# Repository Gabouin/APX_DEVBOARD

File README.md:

<h1 align="center">
  <br>
  
  <br>
  APX DEVBOARD
  <br>
</h1>

<h4 align="center">
A STM32 based devboard with Buttons, a LED and 8 GPIO pins.
</h4>

<div align="center">

</div>

<p align="center">
  <a href="#about-the-project">About</a> •
  <a href="#repository-structure">Structure</a> •
  <a href="#schematic-on-kicad">Schematic</a> •
  <a href="#pcb-on-kicad">PCB</a> •
  <a href="#CAD">CAD</a> •
  <a href="#bill-of-materials">BOM</a> •
  <a href="#license">License</a> •
  <a href="#credits">Credits</a>
</p>

<br>
<br>

## About the Project

**APX DEVBOARD** is a STM32 based devboard designed with GPIO pins, buttons and an LED

### Features

- **STM32G431CBT6** MCU 32-Bit 170MHz 128KB (128K x 8) FLASH 48-LQFP (7x7)
- **8 GPIO pins** to help make any hardware project
- **GPIO linked LED** to program it without needing an external LED
- **GPIO linked button** to use it without needing an external button
- **BOOT and RESET buttons**
- **USB-C input**
- **Amiri silkscreen** for a professional look
- **Original edge cut** to look cool lol
- **Small size** of 2.3*3.7 cm

## Repository Structure

- `src/` — KiCad and Fusion360 project sources
- `production/` — PCB and CAD fabrication files (Gerbers, BOM, Pick & Place, 3mf)
- `images/` — images used in the README and documentation

## Schematic on KiCad

Source : `src/schem`  

## PCB on KiCad

Source : `src/pcb/`  

<div align="center">
  <table>
    <tr>
      <td valign="bottom"></td>
      <td valign="bottom"></td>
      <td valign="bottom"></td>
  </table>
</div>
<div align="center">
  <table>
    <tr>
      <td valign="bottom"></td>
      <td valign="bottom"></td>
  </table>
</div>  

> The PCB design is made on only 2 layers, to reduce the cost of the board !  

<br>

## Share Links

go check out the pcb on [KiCanva](https://kicanvas.org/?github=https://github.com/Gabouin/APX_DEVBOARD/blob/main/src/APX%20Devboard.kicad_pcb) !
<br>
go check out the case on [Fusion360](https://a360.co/4uNEBf6) !

<br>

## CAD

Source : `src/CAD` and
         `production/CAD`

<div align="center">
  <table>
    <tr>
      <td valign="bottom"></td>
      <td></td>
    </tr>
  </table>
</div>

> The case use snap fits as there is no mounting hole in the PCB.

<br>

## Bill of Materials

Source: `production/pcb/bom.csv`

|Designator                       |Footprint                       |Quantity|Value           |LCSC Part #|
|---------------------------------|--------------------------------|--------|----------------|-----------|
|PA2                              |0603                            |1       |LED             |C2286      |
|BOOT                             |SW-SMD_L3.9-W3.0-P4.45          |1       |BOOT            |C455280    |
|C11, C12, C5, C6, C8             |0603                            |5       |1uF             |C15849     |
|C1, C10, C2, C3, C4, C7          |0603                            |6       |100nF           |C14663     |
|C9                               |0603                            |1       |10nF            |C57112     |
|DEBUG                            |PinHeader_1x04_P2.54mm_Vertical |1       |Conn_01x04      |C2691448   |
|J1                               |PinHeader_1x05_P2.54mm_Vertical |1       |Header Left     |C124379    |
|J2                               |PinHeader_1x05_P2.54mm_Vertical |1       |Header Right    |C124379    |
|PA3                              |SW-SMD_L3.9-W3.0-P4.45          |1       |PA3             |C455280    |
|R1, R2                           |0603                            |2       |100k            |C23186     |
|R3, R4, R7                       |0603                            |3       |10k             |C25804     |
|R6, R5                           |0603                            |2       |5.1k            |C25803     |
|RESET                            |SW-SMD_L3.9-W3.0-P4.45          |1       |RESET           |C455280    |
|STM32                            |LQFP-48_L7.0-W7.0-P0.50-LS9.0-BL|1       |STM32G431CBT6   |C529355    |
|U1                               |SOT-23-3                        |1       |XC6206PxxxMR    |C5446      |
|USB-C1                           |USB-C-SMD_TYPE-C-16PIN-2MD-073  |1       |TYPE-C 16PIN 2MD|C2765186   |

## JLPCB order

<div align="center">
  <table>
    <tr>
      <td valign="bottom"></td>
      <td valign="bottom"></td>
  </table>
</div>  

## You might also like

- [APX USB HUB](https://github.com/gabouin/APX-USB-HUB) - A PTC-secured USB HUB designed for [Macondo - Hack Club](https://macondo.hackclub.com)
- [HackPad](https://github.com/Gabouin/Hackpad) - A 6-keys macropad designed for [Blueprint - Hack Club](https://blueprint.hackclub.com)
- See more in my [github](https://github.com/gabouin)

## License

This project is licensed under the **MIT License** — see the [LICENSE](LICENSE) file for details.

## Credits

This project uses:

- **KiCad** - PCB design and schematic capture
- **JLCPCB** - PCB manufacturing
- **LCSC** - Parts order
- **Figma** - Silkscreen and banner design
- **Fusion 360** - CAD
- **[@NotARoomba](https://github.com/notaroomba)** - Readme template

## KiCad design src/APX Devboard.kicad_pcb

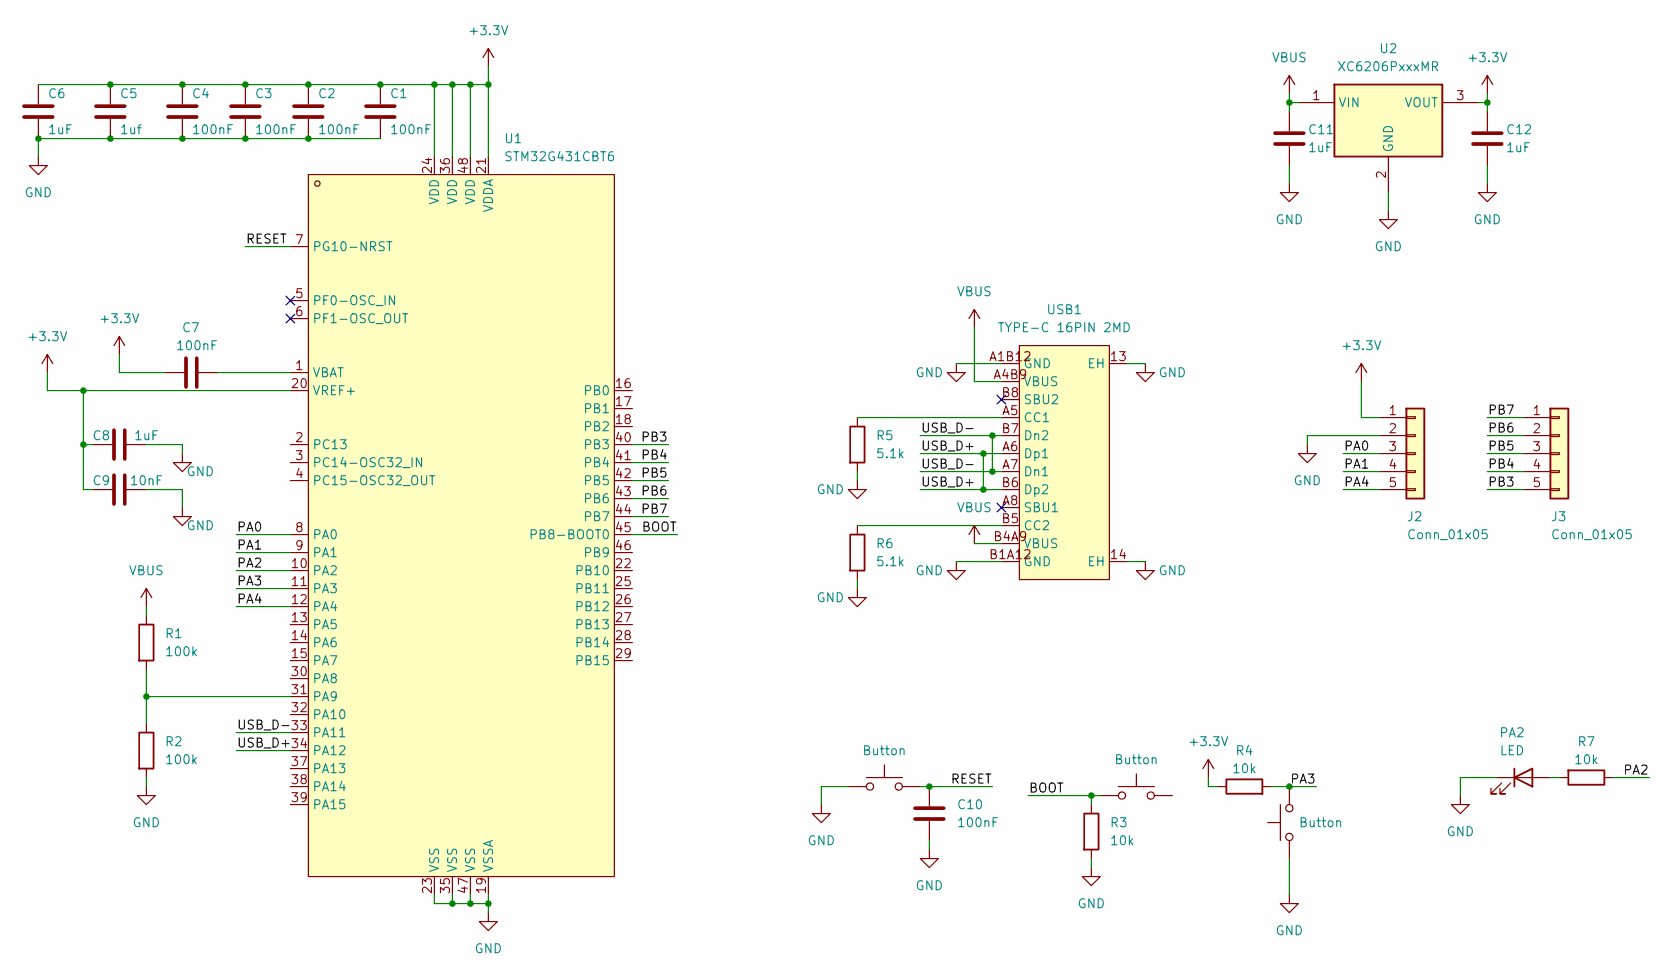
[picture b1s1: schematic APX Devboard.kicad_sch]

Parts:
BOOT1: Button; SW-SMD_L3.9-W3.0-P4.45
C1, C2, C3, C4, C7, C10: 100nF; C_0603_1608Metric
C5: 1uf; C_0603_1608Metric
C6, C8, C11, C12: 1uF; C_0603_1608Metric
C9: 10nF; C_0603_1608Metric
J2, J3: Conn_01x05; PinHeader_1x05_P2.54mm_Vertical
PA2: LED; LED_0603_1608Metric
PA3: Button; SW-SMD_L3.9-W3.0-P4.45
R1, R2: 100k; R_0603_1608Metric
R3, R4, R7: 10k; R_0603_1608Metric
R5, R6: 5.1k; R_0603_1608Metric
RESET1: Button; SW-SMD_L3.9-W3.0-P4.45
U1: STM32G431CBT6; LQFP-48_L7.0-W7.0-P0.50-LS9.0-BL; MPN STM32G431CBT6; LCSC Part C529355
U2: XC6206PxxxMR; SOT-23-3
USB1: TYPE-C 16PIN 2MD; USB-C-SMD_TYPE-C-16PIN-2MD-073; MPN TYPE-C 16PIN 2MD(073); LCSC Part C2765186

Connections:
+3.3V: C1.1, C2.1, C3.1, C4.1, C5.1, C6.1, C7.1, C8.2, C9.2, C12.1, J2.1, R4.1, U1.20 (VREF+), U1.21 (VDDA), U1.24 (VDD), U1.36 (VDD), U1.48 (VDD), U2.3 (VOUT)
/BOOT: BOOT1.1, R3.1, U1.45 (PB8-BOOT0); also elsewhere on the board
/PA0: J2.3, U1.8 (PA0)
/PA1: J2.4, U1.9 (PA1)
/PA2: R7.1, U1.10 (PA2)
/PA3: PA3.2, R4.2, U1.11 (PA3)
/PA4: J2.5, U1.12 (PA4)
/PB3: J3.5, U1.40 (PB3)
/PB4: J3.4, U1.41 (PB4)
/PB5: J3.3, U1.42 (PB5)
/PB6: J3.2, U1.43 (PB6)
/PB7: J3.1, U1.44 (PB7)
/RESET: C10.1, RESET1.2, U1.7 (PG10-NRST); also elsewhere on the board
/USB_D+: U1.34 (PA12), USB1.A6 (Dp1), USB1.B6 (Dp2)
/USB_D-: U1.33 (PA11), USB1.A7 (Dn1), USB1.B7 (Dn2)
GND: C1.2, C2.2, C3.2, C4.2, C5.2, C6.2, C8.1, C9.1, C10.2, C11.2, C12.2, J2.2, PA2.1 (K), PA3.1, R2.2, R3.2, R5.2, R6.2, RESET1.1, U1.19 (VSSA), U1.23 (VSS), U1.35 (VSS), U1.47 (VSS), U2.2 (GND), USB1.13 (EH), USB1.14 (EH), USB1.A1B12 (GND), USB1.B1A12 (GND); also elsewhere on the board
unnamed: PA2.2 (A), R7.2
unnamed: R1.2, R2.1, U1.31 (PA9)
unnamed: C7.2, U1.1 (VBAT)
unnamed: R5.1, USB1.A5 (CC1)
unnamed: R6.1, USB1.B5 (CC2)
VBUS: C11.1, R1.1, U2.1 (VIN), USB1.A4B9 (VBUS), USB1.B4A9 (VBUS)

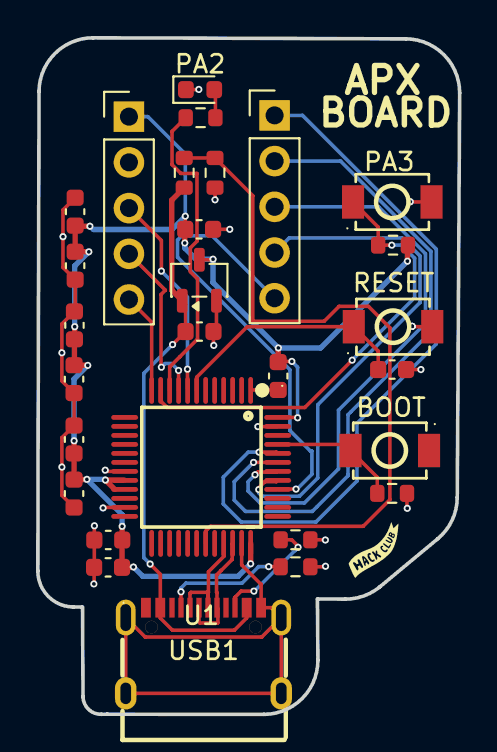
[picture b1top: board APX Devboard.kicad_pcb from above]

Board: 2 copper layers, 23.4 x 37.6 mm, 28 parts (0 on the bottom side), 22 nets.

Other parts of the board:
BOOT: Button; SW-SMD_L3.9-W3.0-P4.45
RESET: Button; SW-SMD_L3.9-W3.0-P4.45

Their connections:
/BOOT: BOOT.1; also elsewhere on the board
/RESET: RESET.2; also elsewhere on the board
GND: RESET.1; also elsewhere on the board

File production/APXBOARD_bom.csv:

"Designator","Footprint","Quantity","Value","LCSC Part #"
"PA2","0603","1","LED","C2286"
"BOOT","SW-SMD_L3.9-W3.0-P4.45","1","BOOT","C455280"
"C11, C12, C5, C6, C8","0603","5","1uF","C15849"
"C1, C10, C2, C3, C4, C7","0603","6","100nF","C14663"
"C9","0603","1","10nF","C57112"
"DEBUG","PinHeader_1x04_P2.54mm_Vertical","1","Conn_01x04","C2691448"
"J1","PinHeader_1x05_P2.54mm_Vertical","1","Header Left","C124379"
"J2","PinHeader_1x05_P2.54mm_Vertical","1","Header Right","C124379"
"PA3","SW-SMD_L3.9-W3.0-P4.45","1","PA3","C455280"
"R1, R2","0603","2","100k","C23186"
"R3, R4, R7","0603","3","10k","C25804"
"R6, R5","0603","2","5.1k","C25803"
"RESET","SW-SMD_L3.9-W3.0-P4.45","1","RESET","C455280"
"STM32","LQFP-48_L7.0-W7.0-P0.50-LS9.0-BL","1","STM32G431CBT6","C529355"
"U1","SOT-23-3","1","XC6206PxxxMR","C5446"
"USB-C1","USB-C-SMD_TYPE-C-16PIN-2MD-073","1","TYPE-C 16PIN 2MD","C2765186"

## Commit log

2026-05-11 Rename APX Devboard.kicad_pro to src/APX Devboard.kicad_pro
2026-05-11 Rename APXBOARD_gerbers.zip to production/APXBOARD_gerbers.zip
2026-05-11 Rename Capture d'écran 2026-05-12 010013.png to images/banner.png
2026-05-11 Create LICENSE
2026-05-18 Rename APX Devboard.step to board.step
2026-05-18 Rename src/board.step to src/CAD/board.step
2026-05-18 Rename production/case bottom.3mf to production/CAD/case bottom.3mf
2026-05-18 Rename production/case top.3mf to production/CAD/case top.3mf

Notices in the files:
README.md:
License: MIT
